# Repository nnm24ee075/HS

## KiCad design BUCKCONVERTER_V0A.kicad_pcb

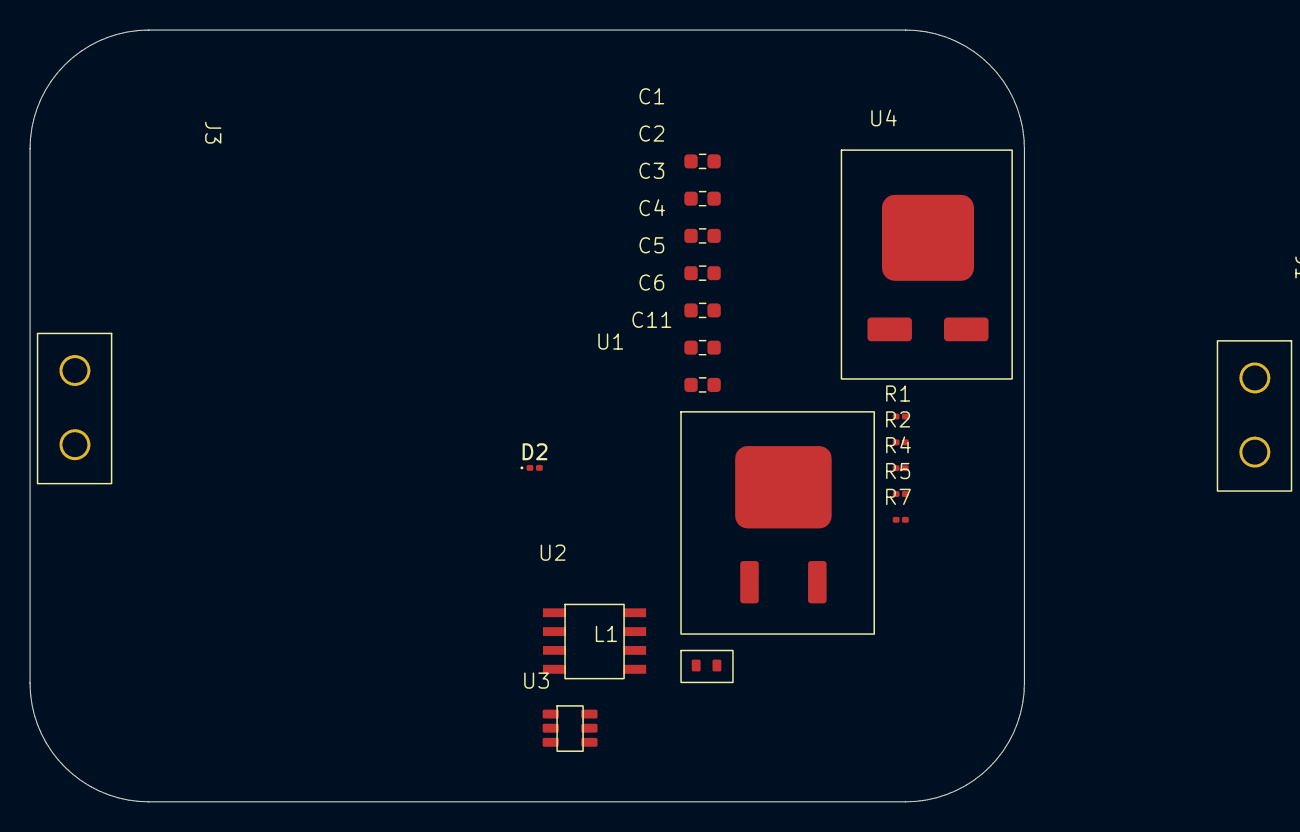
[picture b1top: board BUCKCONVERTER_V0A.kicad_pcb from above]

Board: 2 copper layers, 67.0 x 52.0 mm, 20 parts (0 on the bottom side), 8 nets, no tracks yet.

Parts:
C1, C3: 220pF; C0603
C2, C4, C11: 0.1uF; C0603
C5, C6: 1uF; C0603
D2: shockley diode; D_0201_0603Metric
J1: output terminal; terminal_2x1
J3: inpit terminal; terminal_2x1
L1: 10uH; Inductor
R1: 5; R0603
R2, R7: 5k; R0603
R4: 12k; R0603
R5: 10k; R0603
U1: N-Mosfet
U2: TLC555C; SOIC_8
U3: UCC27511; UCC
U4: 7809

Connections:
+9V: C2.2, C4.2, C6.1, C11.1, R5.2, U1.3 (S), U2.4 (RESET), U2.8 (VDD), U4.3 (OUT)
/Vg: R2.2, R7.2, U1.2 (G)
GND: C1.1, C2.1, C3.2, C4.1, C5.1, C6.2, C11.2, D2.1, J1.2, J3.2, R1.1, U2.1 (GND), U4.2 (GND)
unnamed: C1.2, J1.1, L1.2, R1.2
unnamed: D2.2 (K), L1.1, U1.1 (D)
unnamed: R4.1, R5.1, U2.7 (DIS)
unnamed: C3.1, R4.2, U2.2 (TRIG), U2.6 (THRES)
unnamed: C5.2, J3.1, U4.1 (in)
